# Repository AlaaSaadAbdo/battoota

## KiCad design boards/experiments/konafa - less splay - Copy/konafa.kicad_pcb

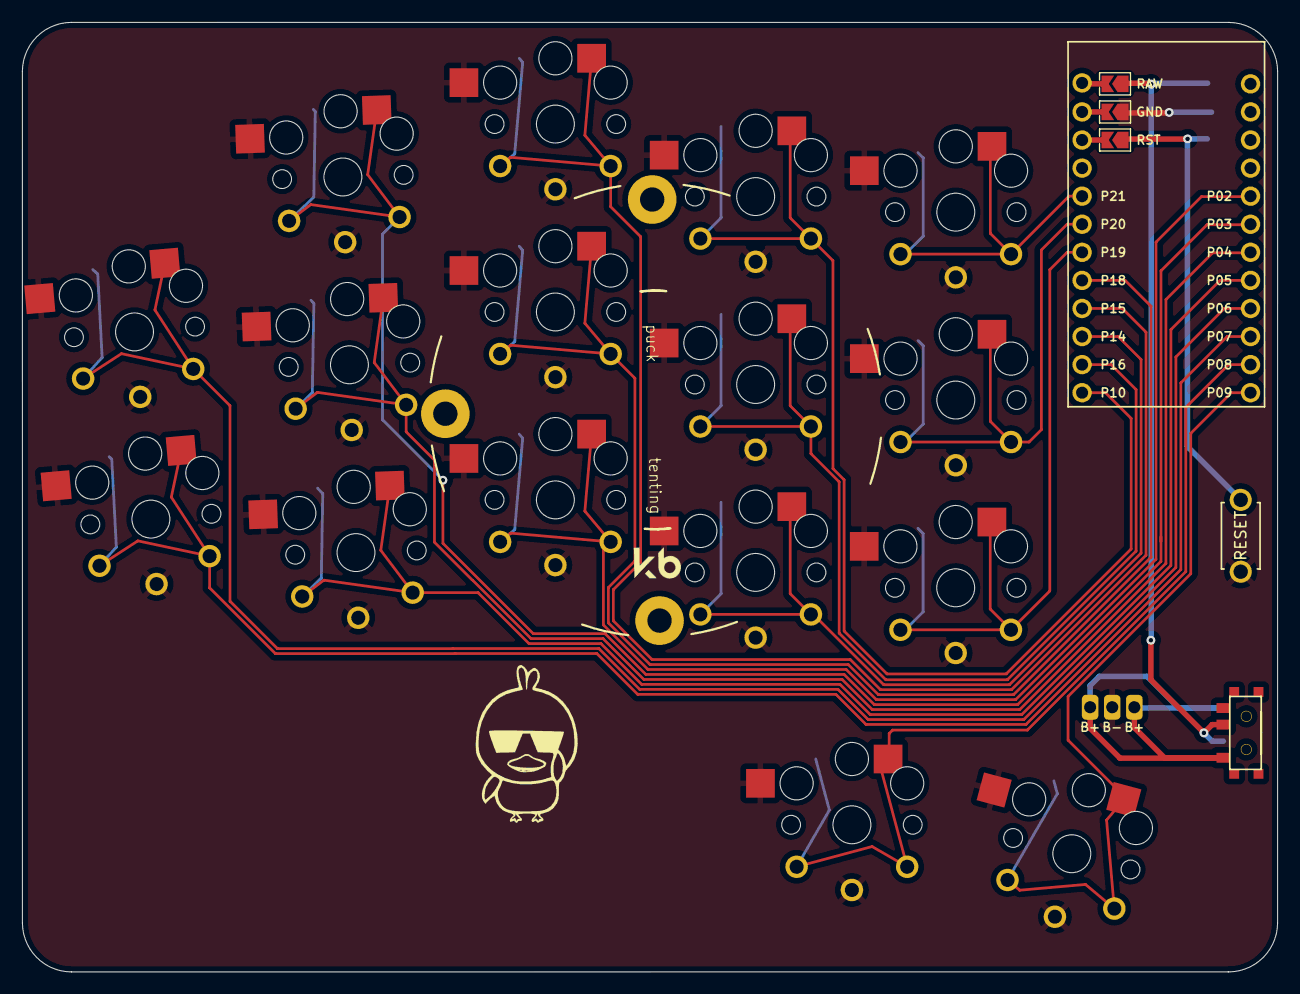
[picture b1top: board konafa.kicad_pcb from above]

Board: 2 copper layers, 113.6 x 85.9 mm, 21 parts (0 on the bottom side), 20 nets.

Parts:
B1: ResetSW
MCU1: ProMicro
PAD1: bat
S3, S5, S7, S9, S11, S13, S15, S17, S19, S21, S23, S27, S27#2, S29, S31, S33: key
T1, T2: SPDT_C128955

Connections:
Braw: PAD1.1, PAD1.3, T1.1, T2.1
GND: B1.2, MCU1.2, PAD1.2, S3.2, S5.2, S7.2, S9.2, S11.2, S13.2, S15.2, S17.2, S19.2, S21.2, S23.2, S27.2, S27#2.2, S29.2, S31.2, S33.2
P2: MCU1.17, S13.1
P3: MCU1.18, S11.1
P4: MCU1.19, S9.1
P5: MCU1.20, S7.1
P6: MCU1.21, S5.1
P7: MCU1.22, S3.1
P8: MCU1.23, S31.1
P9: MCU1.24, S33.1
P10: MCU1.12, S23.1
P14: MCU1.10, S19.1
P15: MCU1.9, S17.1
P16: MCU1.11, S21.1
P18: MCU1.8, S15.1
P19: MCU1.7, S27#2.1
P20: MCU1.6, S27.1
P21: MCU1.5, S29.1
RAW: MCU1.1, T1.2, T2.2
RST: B1.1, MCU1.3

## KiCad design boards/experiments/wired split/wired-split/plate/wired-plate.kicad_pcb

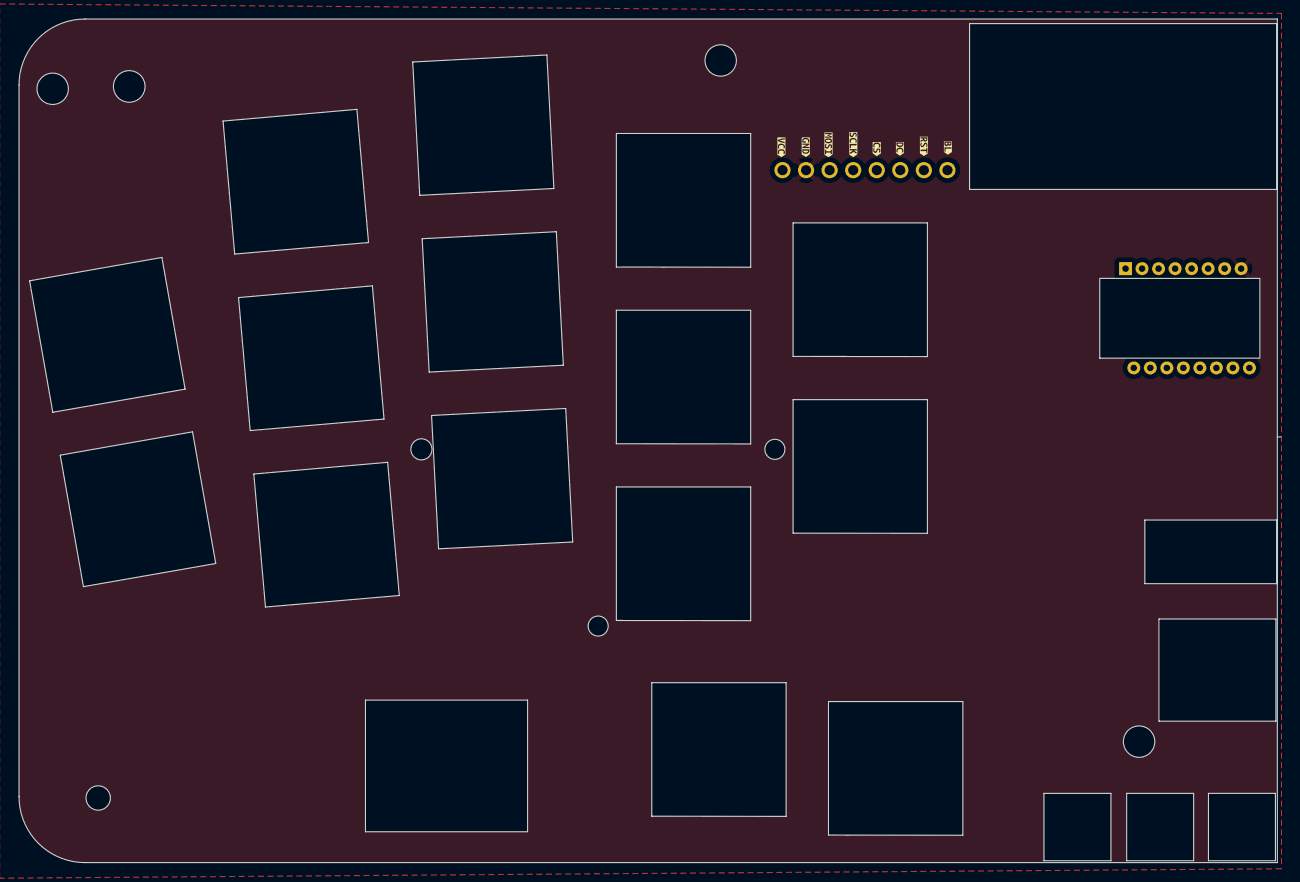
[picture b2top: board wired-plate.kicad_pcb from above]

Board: 2 copper layers, 135.6 x 90.9 mm, 17 parts (1 on the bottom side), 4 nets, no tracks yet.

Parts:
J1: Conn_01x08_Female; Screen Dupont
SW1, SW2, SW3, SW5, SW6, SW7, SW9, SW10, SW11, SW13, SW14, SW15, SW17, SW18, SW19: SW_Push; 14mm-switch-hole
U4: PMW3360DM-T2QU

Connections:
GND_L: J1.2, U4.8 (GND)
MOSI_L: J1.3, U4.11 (MOSI)
SCLK_L: J1.4, U4.10 (SCLK)
VCC_L: J1.1, U4.5 (VDDIO)

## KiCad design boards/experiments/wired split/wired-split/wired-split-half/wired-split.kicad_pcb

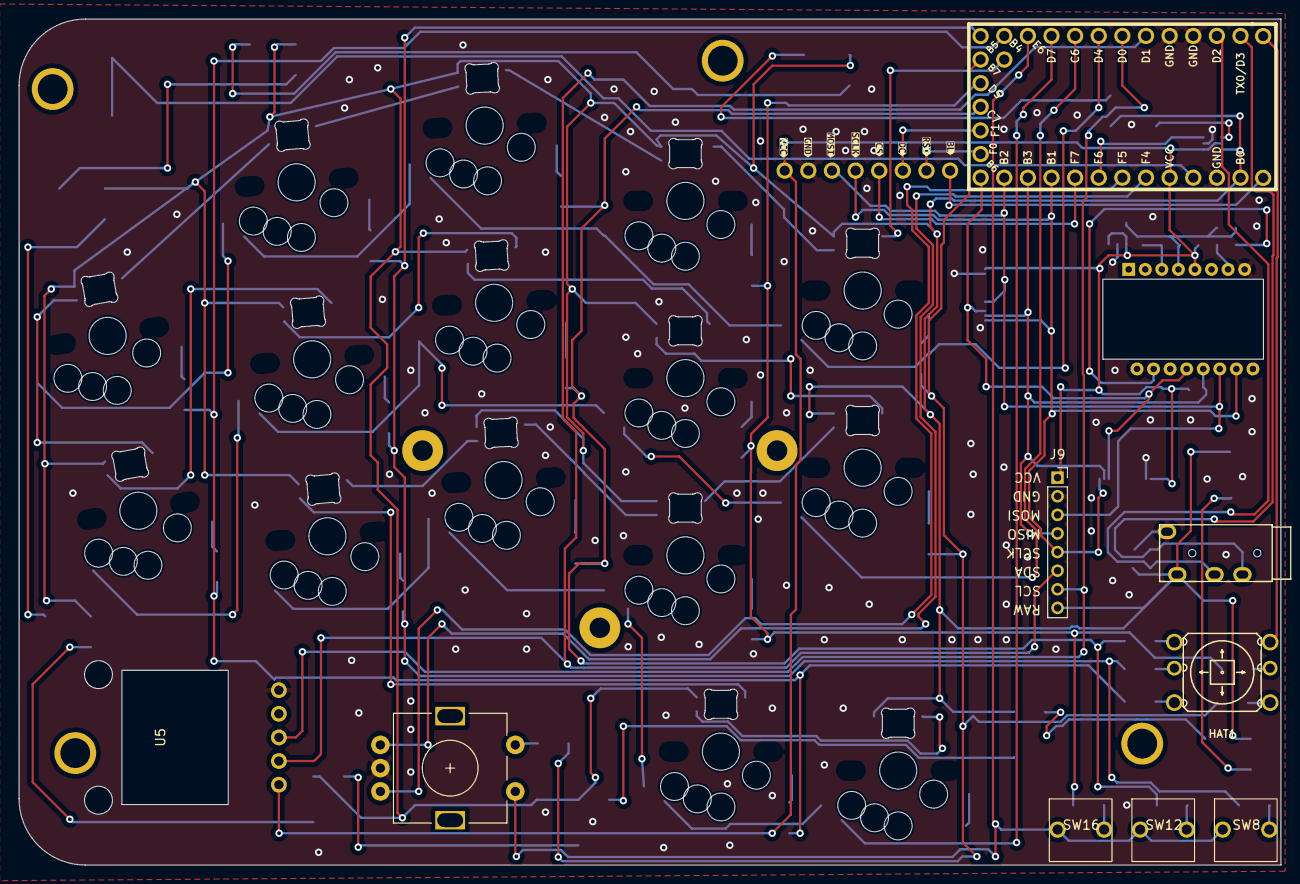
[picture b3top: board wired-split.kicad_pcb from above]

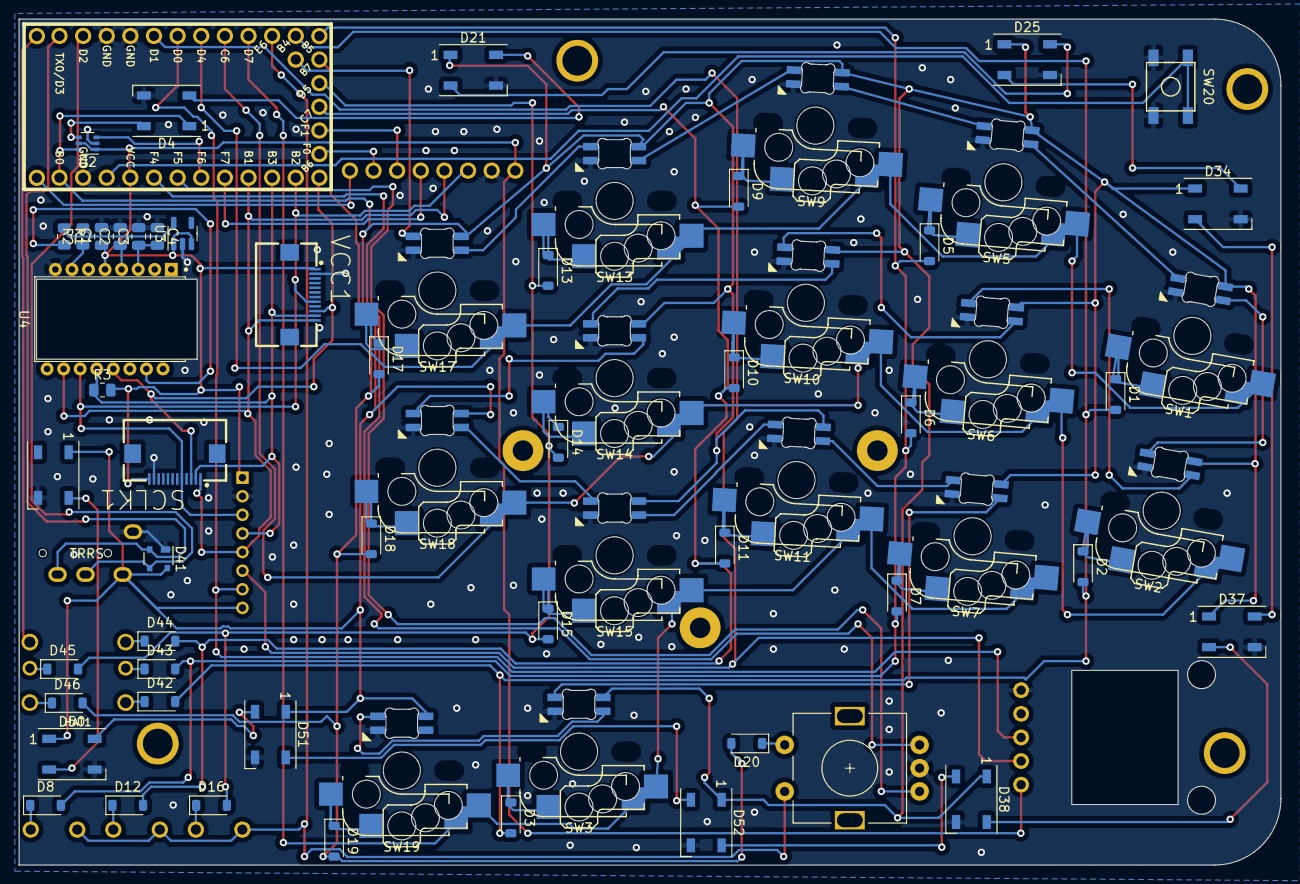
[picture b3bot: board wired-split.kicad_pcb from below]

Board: 2 copper layers, 135.6 x 90.9 mm, 88 parts (48 on the bottom side), 82 nets.

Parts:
C1, C4: 0.1uF; C_0805_2012Metric
C2: 1uF; C_0805_2012Metric
C3: 4.7uF; C_0805_2012Metric
D1, D2, D3, D5, D6, D7, D8, D9, D10, D11, D12, D13, D14, D15, D16, D17, D18, D19, D20, D42, D43, D44, D45, D46: 1N4148; D_SOD-123
D4, D21, D25, D34, D37, D38, D49, D50, D51, D52: WS2812B; LED_WS2812B_PLCC4_5.0x5.0mm_P3.2mm
D22, D23, D24, D26, D27, D28, D29, D30, D31, D32, D33, D35, D36, D39, D40: SK6812MINI-E; MX_SK6812MINI-E_REV
D41: PRTR5V0U2X; SOT-143
HAT1: 5Way-Tactile_K1-1506DN-01; 5Way-non-reverse
J1: Conn_01x08_Female; Screen Dupont
J2: AudioJack4dpb; TRRS-PJ-320A
J3, J4: Conn_01x12_Female; FPC-SMD_FPC05012-09200-.5mm-rev
J9: Conn_01x08; PinSocket_1x08_P2.00mm_Vertical
R1: 39; R_0805_2012Metric
R2, R3: 10K; R_0805_2012Metric
SW1, SW2, SW3, SW5, SW6, SW7, SW9, SW10, SW11, SW13, SW14, SW15, SW17, SW18, SW19: SW_Push; Kailh_hotswap_only_MX-CHOC
SW8, SW12, SW16: SW_Push; Silent Square Micro Switch
SW20: SW_Push; SKQG-1155865
SW21: Rotary_Encoder_Switch; RotaryEncoder_Alps_EC11E-Switch_Vertical_H20mm-keebio_modif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
U1: Helios
U2: 74LVC1T45; SOT-363_SC-70-6
U3: TCR2EF19,LM(CT; SOT-23-5
U4: PMW3360DM-T2QU
U5: DRV2605L; Pimoroni Haptic Buzz DRV2605L Driver

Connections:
Backlight_L: D4.4 (DIN), U2.4 (B)
EncL_L: SW21.A, U1.20 (A3/PF4)
EncR_L: SW21.B, U1.19 (A2/PF5)
GND_L: C1.2, C2.2, C3.2, C4.1, D4.3 (VSS), D21.3 (VSS), D22.3 (VSS), D23.3 (VSS), D24.3 (VSS), D25.3 (VSS), D26.3 (VSS), D27.3 (VSS), D28.3 (VSS), D29.3 (VSS), D30.3 (VSS), D31.3 (VSS), D32.3 (VSS), D33.3 (VSS), D34.3 (VSS), D35.3 (VSS), D36.3 (VSS), D37.3 (VSS), D38.3 (VSS), D39.3 (VSS), D40.3 (VSS), D41.1 (GND), D49.3 (VSS), D50.3 (VSS), D51.3 (VSS), D52.3 (VSS), J1.2, J2.C, J3.2, J4.11, J9.2, SW20.2, SW21.C, U1.3 (GND), U1.4 (GND), U1.23 (GND), U2.2 (GND), U3.2 (GND), U4.8 (GND), U5.5 (GND)
LED_5V_L: D22.4 (DIN), U1.30 (RGB)
MISO_L: J3.11, J4.2, J9.4, R3.1, U1.15 (14/PB3), U4.12 (MISO)
MOSI_L: J1.3, J3.8, J4.5, J9.3, U1.14 (16/PB2), U4.11 (MOSI)
NCS_L: J3.10, J4.3, U1.13 (10/PB6), U4.13 (~NCS)
unnamed: D1.1 (K), SW1.2
unnamed: D2.1 (K), SW2.2
unnamed: D3.1 (K), SW3.2
unnamed: D5.1 (K), SW5.2
unnamed: D6.1 (K), SW6.2
unnamed: D7.1 (K), SW7.2
unnamed: D8.1 (K), SW8.2
unnamed: D9.1 (K), SW9.2
unnamed: D10.1 (K), SW10.2
unnamed: D11.1 (K), SW11.2
unnamed: D12.1 (K), SW12.2
unnamed: D13.1 (K), SW13.2
unnamed: D14.1 (K), SW14.2
unnamed: D15.1 (K), SW15.2
unnamed: D16.1 (K), SW16.2
unnamed: D17.1 (K), SW17.2
unnamed: D18.1 (K), SW18.2
unnamed: D19.1 (K), SW19.2
unnamed: D20.1 (K), SW21.S2
unnamed: D4.2 (DOUT), D21.4 (DIN)
unnamed: D21.2 (DOUT), D25.4 (DIN)
unnamed: D22.2 (DOUT), D26.4 (DIN)
unnamed: D23.4 (DIN), D39.2 (DOUT)
unnamed: D23.2 (DOUT), D27.4 (DIN)
unnamed: D24.4 (DIN), D40.2 (DOUT)
unnamed: D24.2 (DOUT), D28.4 (DIN)
unnamed: D25.2 (DOUT), D34.4 (DIN)
unnamed: D26.2 (DOUT), D29.4 (DIN)
unnamed: D27.2 (DOUT), D30.4 (DIN)
unnamed: D28.2 (DOUT), D31.4 (DIN)
unnamed: D29.2 (DOUT), D32.4 (DIN)
unnamed: D30.2 (DOUT), D33.4 (DIN)
unnamed: D32.2 (DOUT), D35.4 (DIN)
unnamed: D33.2 (DOUT), D36.4 (DIN)
unnamed: D34.2 (DOUT), D37.4 (DIN)
unnamed: D35.2 (DOUT), D39.4 (DIN)
unnamed: D36.2 (DOUT), D40.4 (DIN)
unnamed: D37.2 (DOUT), D38.4 (DIN)
unnamed: D38.2 (DOUT), D52.4 (DIN)
unnamed: D42.1 (K), HAT1.1
unnamed: D43.1 (K), HAT1.2
unnamed: D44.1 (K), HAT1.3
unnamed: D45.1 (K), HAT1.5
unnamed: D46.1 (K), HAT1.6
unnamed: D49.4 (DIN), D50.2 (DOUT)
unnamed: D50.4 (DIN), D51.2 (DOUT)
unnamed: D51.4 (DIN), D52.2 (DOUT)
unnamed: U1.18 (A1/PF6), U2.3 (A)
unnamed: R1.2, U4.15 (LED_P)
unnamed: C3.1, C4.2, U4.3 (VDDPIX)
unnamed: R2.1, U4.7 (~NRESET)
RAW_L: D4.1 (VDD), D21.1 (VDD), D22.1 (VDD), D23.1 (VDD), D24.1 (VDD), D25.1 (VDD), D26.1 (VDD), D27.1 (VDD), D28.1 (VDD), D29.1 (VDD), D30.1 (VDD), D31.1 (VDD), D32.1 (VDD), D33.1 (VDD), D34.1 (VDD), D35.1 (VDD), D36.1 (VDD), D37.1 (VDD), D38.1 (VDD), D39.1 (VDD), D40.1 (VDD), D41.4 (VCC), D49.1 (VDD), D50.1 (VDD), D51.1 (VDD), D52.1 (VDD), J2.D, J9.8, U1.24 (B0), U2.6 (VCCB)
RESET_L: SW20.1, U1.22 (RST)
RX_L: D41.3 (I/O2), J2.A, U1.2 (RX1/PD2)
SCLK_L: J1.4, J3.12, J4.1, J9.5, U1.16 (15/PB1), U4.10 (SCLK)
SCL_L: J9.7, U1.6 (3/PD0), U5.3 (SCL)
SDA_L: J9.6, U1.5 (2/PD1), U5.2 (SDA)
TFT_BL_L: J1.8, U1.32 (GPIO11)
TFT_CS_L: J1.5, U1.17 (A0/PF7)
TFT_DC_L: J1.6, U1.28 (F1)
TFT_RST_L: J1.7, U1.29 (F0)
TX_L: D41.2 (I/O1), J2.B, U1.1 (TX0/PD3)
VCC_L: C1.1, J1.1, J3.1, J4.12, J9.1, R3.2, U1.21 (VCC), U2.1 (VCCA), U2.5 (DIR), U3.1 (IN), U3.3 (EN), U4.5 (VDDIO), U5.1 (VDD)
VDD_L: C2.1, R1.1, R2.2, U3.5 (OUT), U4.4 (VDD)
col0_L: D1.2 (A), D2.2 (A), D3.2 (A), D42.2 (A), U1.11 (8/PB4)
col1_L: D5.2 (A), D6.2 (A), D7.2 (A), D8.2 (A), D43.2 (A), U1.12 (9/PB5)
col2_L: D9.2 (A), D10.2 (A), D11.2 (A), D12.2 (A), D44.2 (A), U1.27 (C7)
col3_L: D13.2 (A), D14.2 (A), D15.2 (A), D16.2 (A), D45.2 (A), U1.26 (D5)
col4_L: D17.2 (A), D18.2 (A), D19.2 (A), D20.2 (A), D46.2 (A), U1.25 (B7)
row_0_L: SW1.1, SW5.1, SW9.1, SW13.1, SW17.1, U1.7 (4/PD4)
row_1_L: SW2.1, SW6.1, SW10.1, SW14.1, SW18.1, U1.8 (5/PC6)
row_2_L: SW3.1, SW7.1, SW11.1, SW15.1, SW19.1, U1.9 (6/PD7)
row_3_L: SW8.1, SW12.1, SW16.1, SW21.S1, U1.10 (7/PE6)
row_4_L: HAT1.4, U1.31 (GPIO10)

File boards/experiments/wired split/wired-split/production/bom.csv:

Designator,Footprint,Quantity,Value,LCSC Part #
C1,0805,1,0.1uF,C77456
C2,0805,1,1uF,C366879
C3,0805,1,4.7uF,C303940
C4,0805,1,0.1uF,C77456
"D1, D10, D11, D12, D13, D14, D15, D16, D17, D18, D19, D2, D20, D3, D42, D43, D44, D45, D46, D5, D6, D7, D8, D9",D_SOD-123,24,1N4148,C8598
"D21, D25, D34, D37, D38, D4, D49, D50, D51, D52",LED_WS2812B_PLCC4_5.0x5.0mm_P3.2mm,10,WS2812B,
"D22, D23, D24, D26, D27, D28, D29, D30, D31, D32, D33, D35, D36, D39, D40",MX_SK6812MINI-E_REV,15,SK6812MINI-E,
D41,SOT-143,1,PRTR5V0U2X,C12333
HAT1,5Way-non-reverse,1,5Way-Tactile_K1-1506DN-01,
J1,Screen Dupont,1,Conn_01x08_Female,
J2,TRRS-PJ-320A,1,AudioJack4dpb,
R1,0805,1,39,C514993
R2,0805,1,10K,C406725
R3,0805,1,10K,C406725
"SW1, SW10, SW11, SW13, SW14, SW15, SW17, SW18, SW19, SW2, SW3, SW5, SW6, SW7, SW9",Kailh_hotswap_only_MX-CHOC,15,SW_Push,
"SW12, SW16, SW8",Silent Square Micro Switch,3,SW_Push,
SW20,SKQG-1155865,1,SW_Push,C221856
SW21,RotaryEncoder_Alps_EC11E-Switch_Vertical_H20mm-keebio_modified,1,Rotary_Encoder_Switch,
U1,Helios,1,Helios,
U2,SOT-363_SC-70-6,1,74LVC1T45,C139353
U3,SOT-23-5,1,"TCR2EF19,LM(CT",C146366
U4,PMW3360DM-T2QU,1,PMW3360DM-T2QU,
U5,Pimoroni Haptic Buzz DRV2605L Driver,1,DRV2605L,

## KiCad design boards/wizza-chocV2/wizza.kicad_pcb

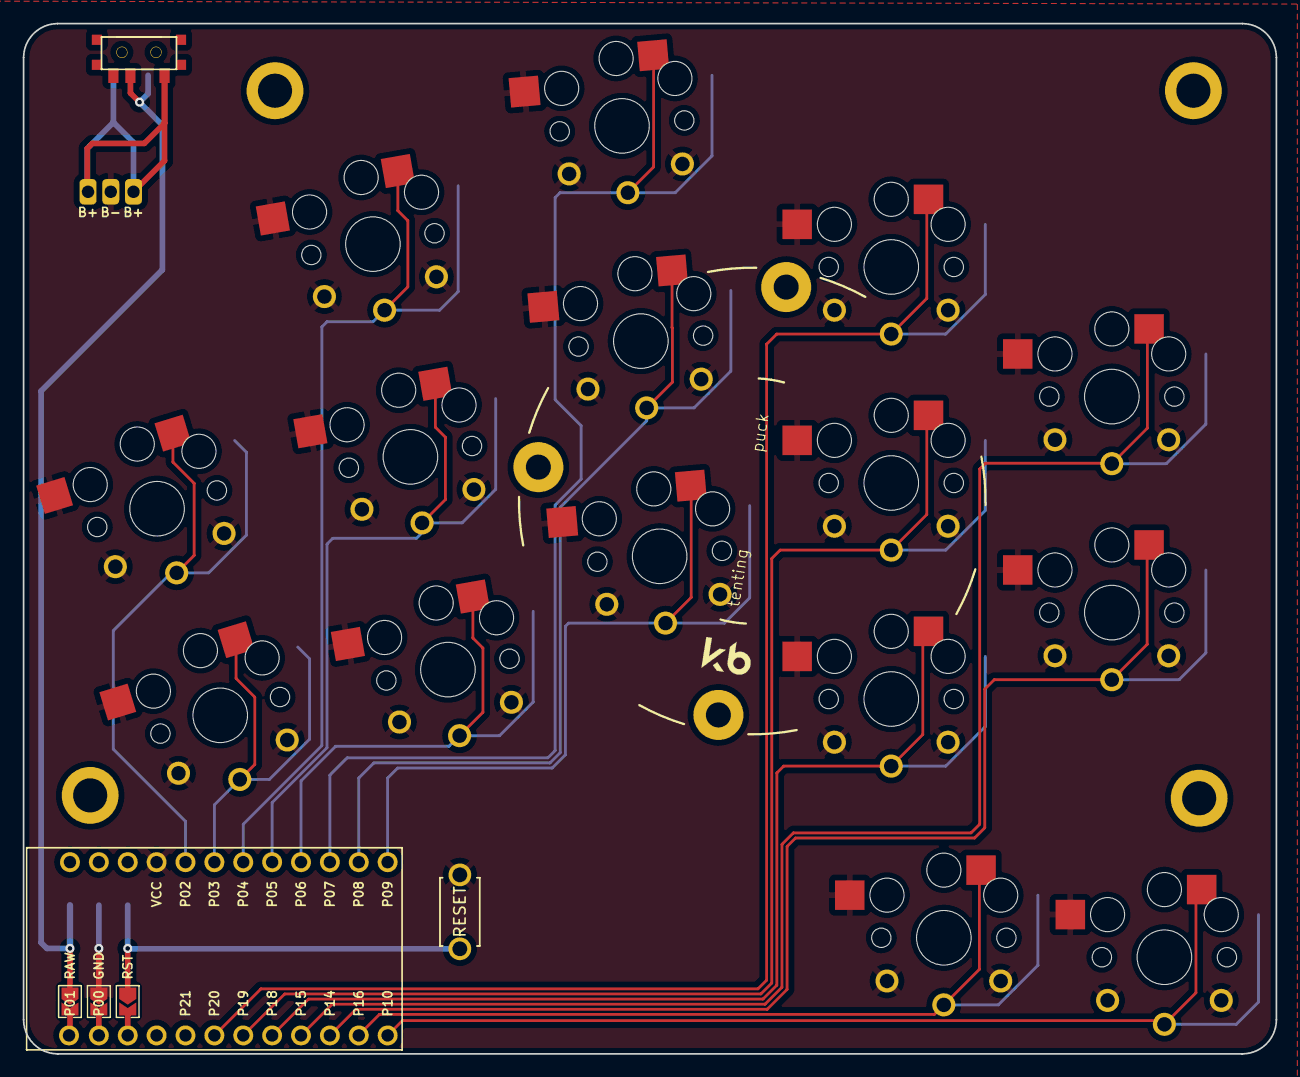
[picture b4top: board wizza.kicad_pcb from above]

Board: 2 copper layers, 110.2 x 90.6 mm, 20 parts (0 on the bottom side), 19 nets.

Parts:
B1: ResetSW
MCU1: ProMicro32keys
PAD1: bat
S1, S2, S3, S4, S5, S6, S7, S8, S9, S10, S11, S12, S13, S14, S15: ChocV2hotswap
T1, T2: SPDT_C128955

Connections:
GND: B1.2, MCU1.2, MCU1.16, PAD1.2, S1.1, S2.1, S3.1, S4.1, S5.1, S6.1, S7.1, S8.1, S9.1, S10.1, S11.1, S12.1, S13.1, S14.1, S15.1
RAW: MCU1.1, T1.2, T2.2
RST: B1.1, MCU1.3
b+: PAD1.1, PAD1.3, T1.1, T2.1
matrix_index_bottom: MCU1.8, S9.2
matrix_index_home: MCU1.7, S10.2
matrix_index_top: MCU1.6, S11.2
matrix_inner_bottom: MCU1.10, S12.2
matrix_inner_home: MCU1.9, S13.2
matrix_middle_bottom: MCU1.24, S6.2
matrix_middle_home: MCU1.23, S7.2
matrix_middle_top: MCU1.22, S8.2
matrix_pinky_home: MCU1.18, S1.2
matrix_pinky_top: MCU1.17, S2.2
matrix_ring_bottom: MCU1.21, S3.2
matrix_ring_home: MCU1.20, S4.2
matrix_ring_top: MCU1.19, S5.2
thumb_reachy: MCU1.12, S15.2
thumb_tucky: MCU1.11, S14.2

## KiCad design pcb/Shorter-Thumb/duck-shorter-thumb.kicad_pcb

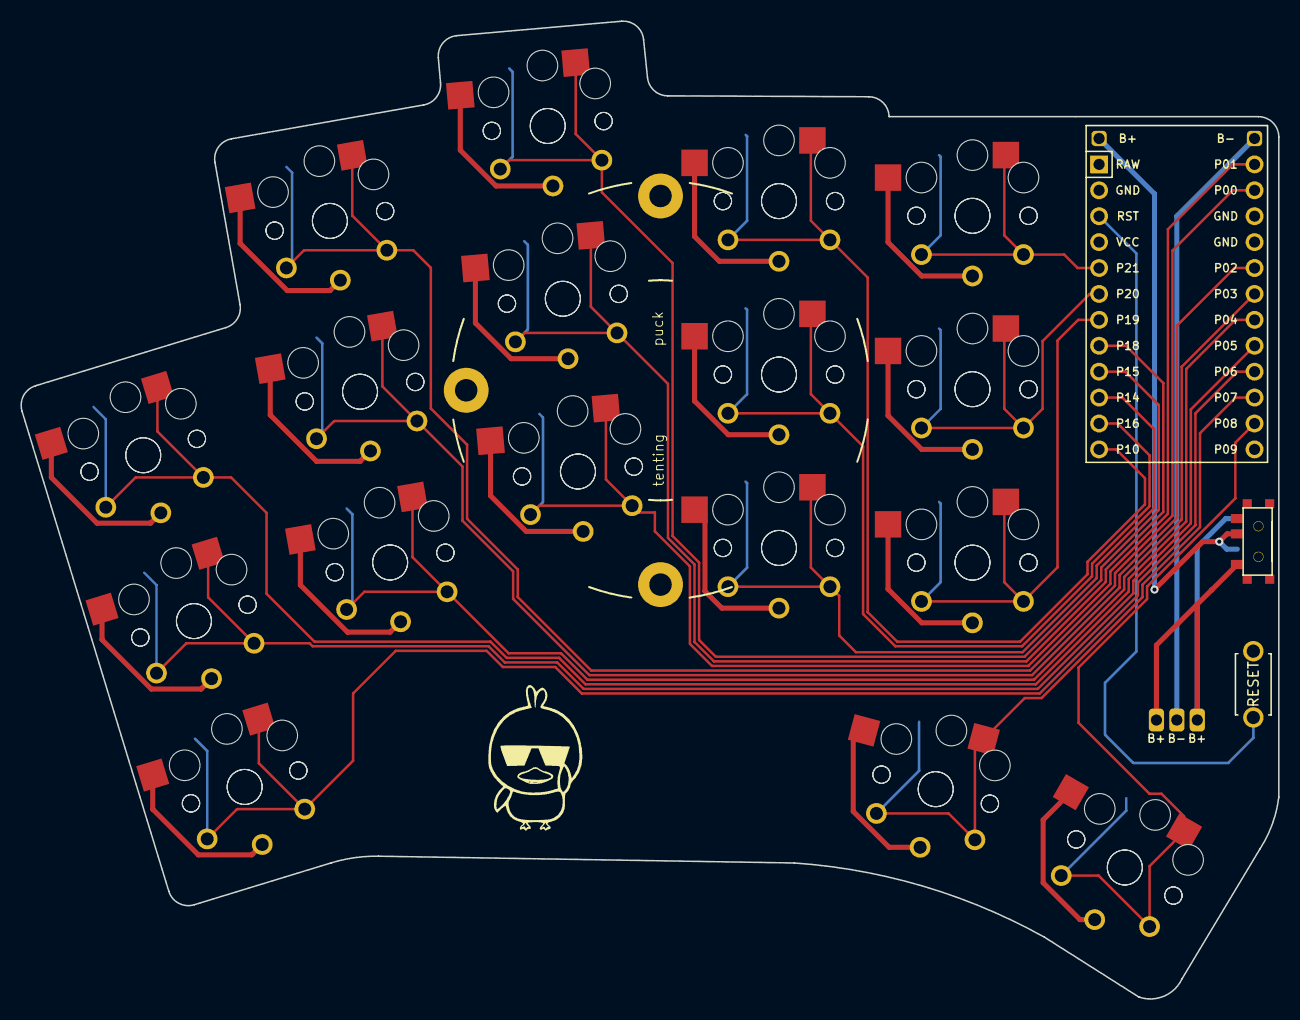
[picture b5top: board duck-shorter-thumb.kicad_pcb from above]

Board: 2 copper layers, 123.3 x 95.9 mm, 39 parts (0 on the bottom side), 22 nets.

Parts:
B1: ResetSW
MCU1: ProMicro
PAD1: bat
S1, S2, S3, S4, S5, S6, S7, S8, S9, S10, S11, S12, S13, S14, S15, S16, S17, S18, S19, S20, S21, S22, S23, S24, S25, S26, S27, S28, S29, S30, S31, S32, S33, S34: PG1350
T1, T2: SPDT_C128955

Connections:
Bminus: MCU1.25, PAD1.2
Bplus: MCU1.25, T1.2, T2.2
Braw: PAD1.1, T1.1, T2.1
GND: B1.2, MCU1.2, MCU1.15, MCU1.16, S1.2, S2.2, S3.2, S4.2, S5.2, S6.2, S7.2, S8.2, S9.2, S10.2, S11.2, S12.2, S13.2, S14.2, S15.2, S16.2, S17.2, S18.2, S19.2, S20.2, S21.2, S22.2, S23.2, S24.2, S25.2, S26.2, S27.2, S28.2, S29.2, S30.2, S31.2, S32.2, S33.2, S34.2
P0: MCU1.14, S11.1, S12.1
P1: MCU1.13, S13.1, S14.1
P2: MCU1.17, S9.1, S10.1
P3: MCU1.18, S7.1, S8.1
P4: MCU1.19, S5.1, S6.1
P5: MCU1.20, S3.1, S4.1
P6: MCU1.21, S1.1, S2.1
P7: MCU1.22, S31.1, S32.1
P8: MCU1.23, S33.1, S34.1
P10: MCU1.12, S23.1, S24.1
P14: MCU1.10, S19.1, S20.1
P15: MCU1.9, S17.1, S18.1
P16: MCU1.11, S21.1, S22.1
P18: MCU1.8, S15.1, S16.1
P19: MCU1.7, S25.1, S26.1
P20: MCU1.6, S27.1, S28.1
P21: MCU1.5, S29.1, S30.1
RST: B1.1, MCU1.3
